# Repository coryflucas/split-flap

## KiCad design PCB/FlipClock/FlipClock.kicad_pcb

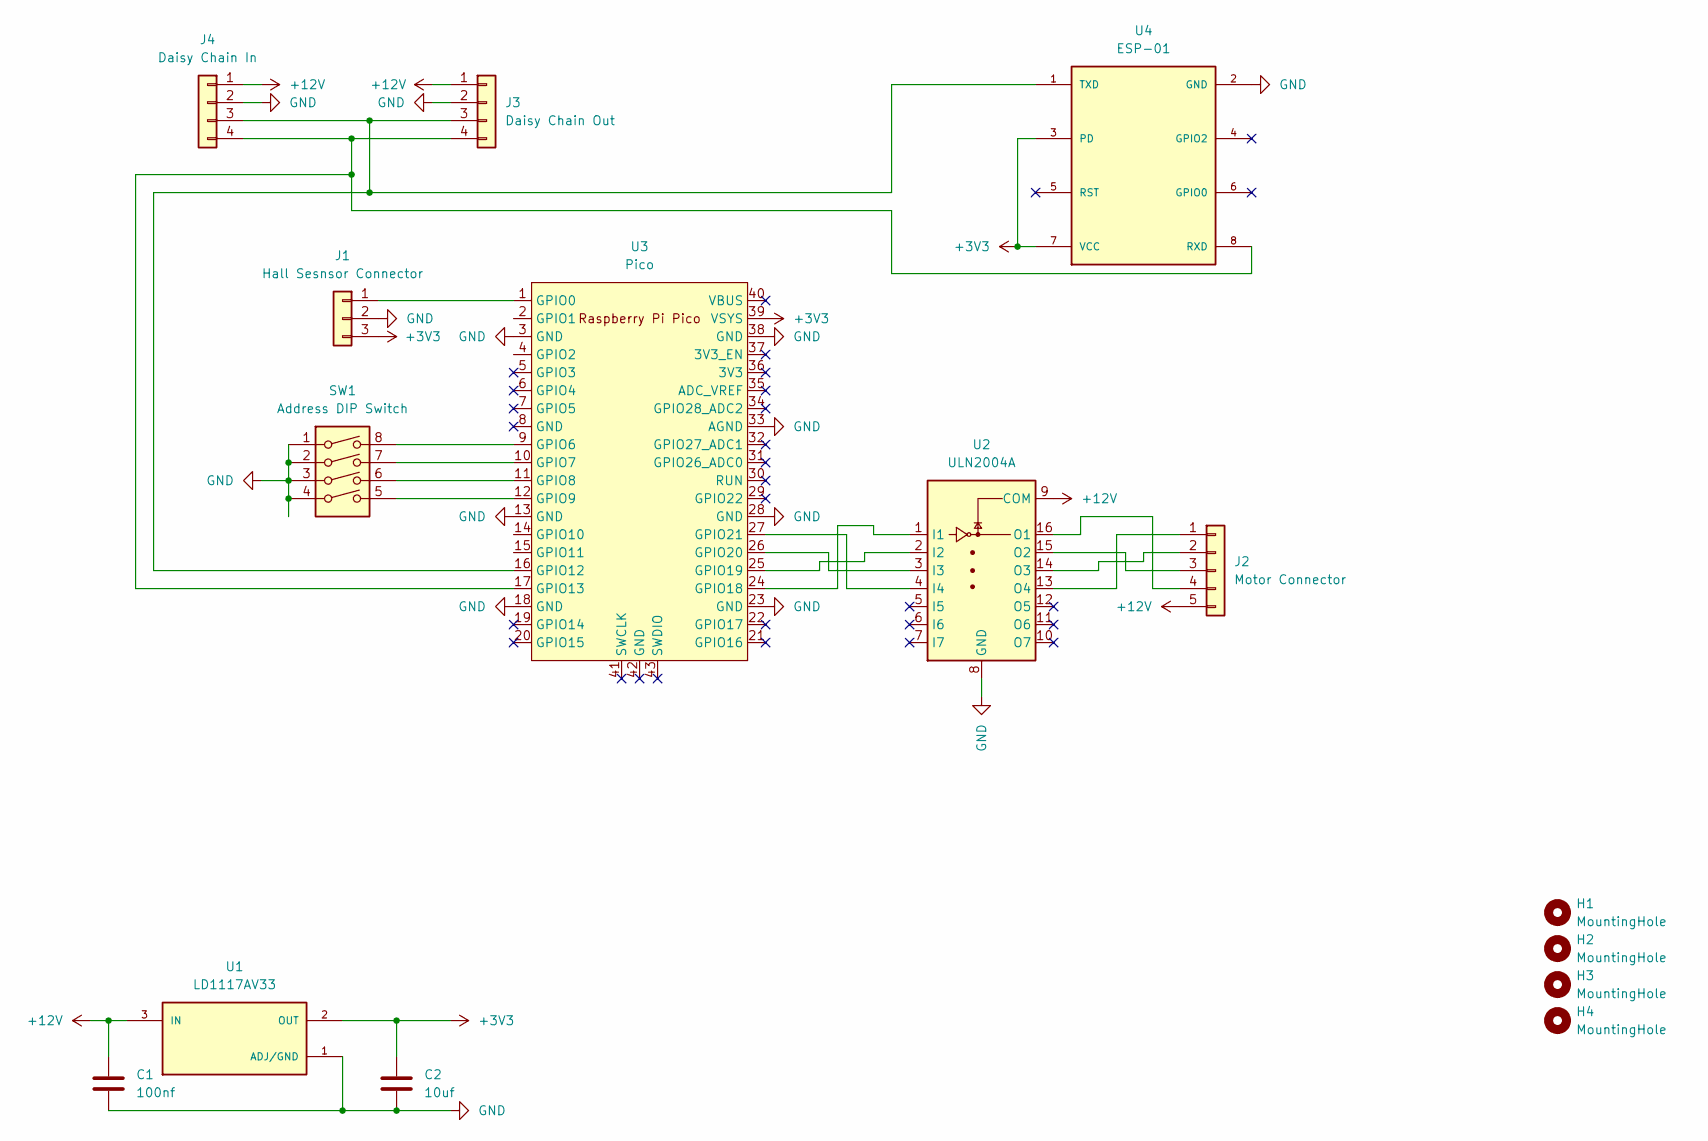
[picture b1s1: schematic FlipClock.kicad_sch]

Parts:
C1: 100nf; CP_EIA-3216-18_Kemet-A_Pad1.58x1.35mm_HandSolder
C2: 10uf; CP_EIA-3216-18_Kemet-A_Pad1.58x1.35mm_HandSolder
H1, H2, H3, H4: MountingHole; MountingHole_3.2mm_M3_ISO14580
J1: Hall Sesnsor Connector; JST_XH_B3B-XH-A_1x03_P2.50mm_Vertical
J2: Motor Connector; JST_XH_B5B-XH-A_1x05_P2.50mm_Vertical
J3: Daisy Chain Out; JST_XH_B4B-XH-A_1x04_P2.50mm_Vertical
J4: Daisy Chain In; JST_XH_B4B-XH-A_1x04_P2.50mm_Vertical
SW1: Address DIP Switch; DIP-8_W7.62mm
U1: LD1117AV33; TO255P1020X450X1968-3; PARTREV 26
U2: ULN2004A; DIP-16_W7.62mm_LongPads
U3: Pico; RPi_Pico_TH
U4: ESP-01

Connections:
+3V3: C2.1, J1.3, U1.2 (OUT), U3.39 (VSYS), U4.3 (PD), U4.7 (VCC)
+12V: C1.1, J2.5, J3.1, J4.1, U1.3 (IN), U2.9 (COM)
GND: C1.2, C2.2, J1.2, J3.2, J4.2, SW1.1, SW1.2, SW1.3, SW1.4, U1.1 (ADJ/GND), U2.8 (GND), U3.3 (GND), U3.13 (GND), U3.18 (GND), U3.23 (GND), U3.28 (GND), U3.33 (AGND), U3.38 (GND), U4.2 (GND)
unnamed: J2.1, U2.13 (O4)
unnamed: J2.2, U2.14 (O3)
unnamed: J2.3, U2.15 (O2)
unnamed: J2.4, U2.16 (O1)
unnamed: J3.3, J4.3, U3.16 (GPIO12), U4.1 (TXD)
unnamed: J3.4, J4.4, U3.17 (GPIO13), U4.8 (RXD)
unnamed: SW1.7, U3.10 (GPIO7)
unnamed: SW1.8, U3.9 (GPIO6)
unnamed: J1.1, U3.1 (GPIO0)
unnamed: SW1.6, U3.11 (GPIO8)
unnamed: SW1.5, U3.12 (GPIO9)
unnamed: U2.1 (I1), U3.24 (GPIO18)
unnamed: U2.2 (I2), U3.25 (GPIO19)
unnamed: U2.3 (I3), U3.26 (GPIO20)
unnamed: U2.4 (I4), U3.27 (GPIO21)

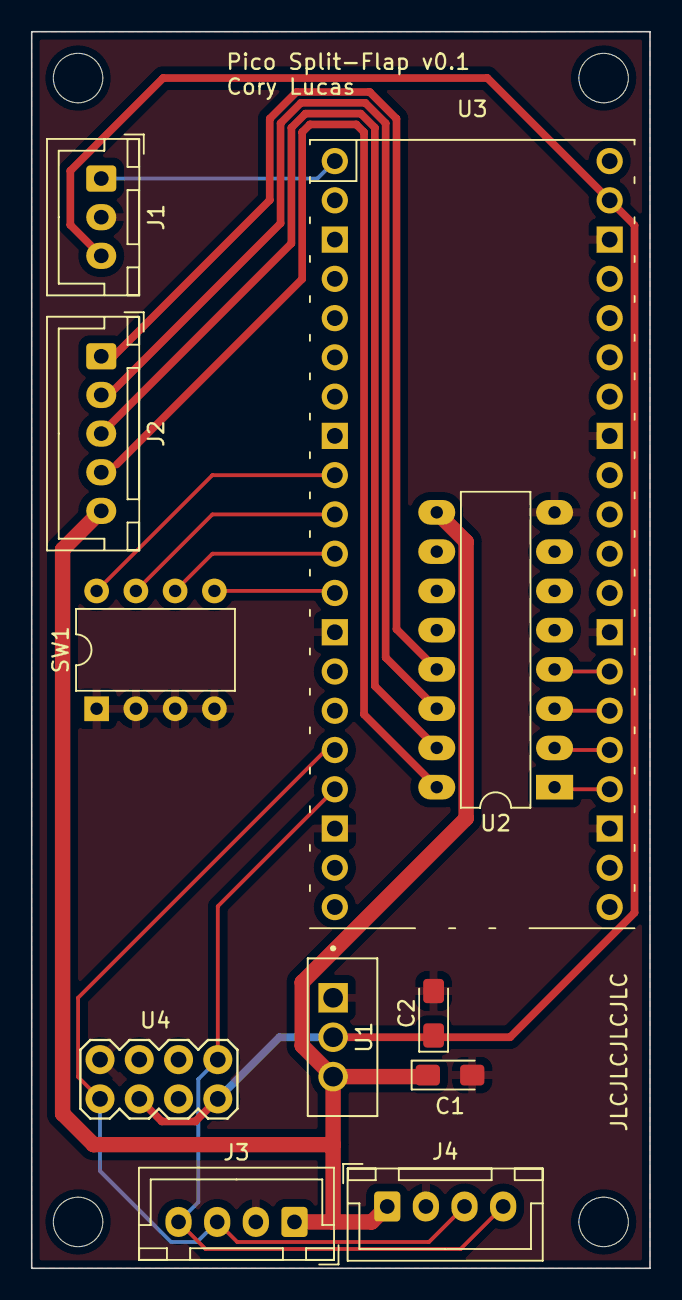
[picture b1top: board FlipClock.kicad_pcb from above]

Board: 2 copper layers, 40.0 x 80.0 mm, 15 parts (0 on the bottom side), 18 nets.

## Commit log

2022-05-25 add v 0.1 pi pico based pcb
